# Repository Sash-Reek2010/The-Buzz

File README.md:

# The Buzz

A PCB which buzzes! You can change the tone and frequency using the potentiometers and make cool buzz combinations! It features the LM556 timer as the main IC here! The buzzers used here are passive piezo buzzers.

## Schematic
The schematic is made in KiCAD!

## PCB
The PCB is also made in KiCAD!

## PCB View & Render

## Try it out!

[KiCanvas Link](https://kicanvas.org/?repo=https%3A%2F%2Fgithub.com%2FSash-Reek2010%2FThe-Buzz%2Ftree%2Fmain%2FSource)

## BOM

| Name | Quantity |
|------|----------|
| Passive Piezo Buzzer | 10 |
| 10uF Capacitor | 2 |
| 10nF Capacitor | 2 |
| 100nF Capacitor | 1 |
| 100uF Capacitor | 1 |
| LM556 IC | 1 |
| USB A Connector | 1 |
| 10k Resistor | 2 |
| 10k Potentiometer | 2 |
| CD4017 IC | 1 |

## Thanks for Reading. - Sashreek!

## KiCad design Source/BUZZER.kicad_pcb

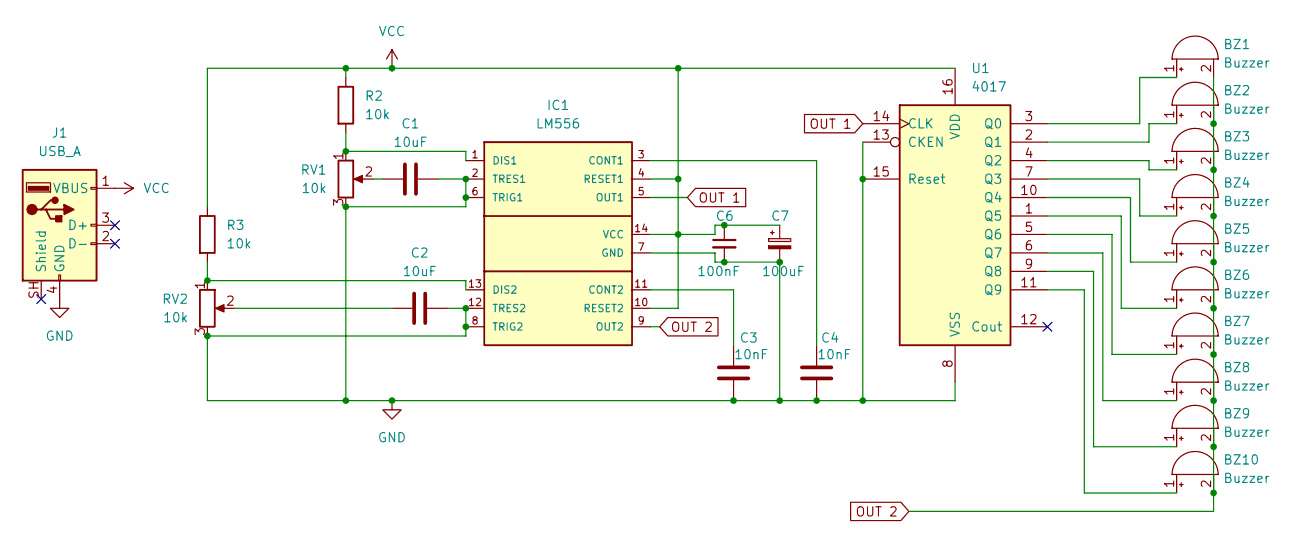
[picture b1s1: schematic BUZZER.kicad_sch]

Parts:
BZ1, BZ2, BZ3, BZ4, BZ5, BZ6, BZ7, BZ8, BZ9, BZ10: Buzzer; Buzzer_12x9.5RM7.6
C1, C2: 10uF; C_Disc_D8.0mm_W5.0mm_P5.00mm
C3, C4: 10nF; C_Disc_D8.0mm_W5.0mm_P5.00mm
C6: 100nF; C_Disc_D8.0mm_W5.0mm_P5.00mm
C7: 100uF; C_Radial_D5.0mm_H11.0mm_P2.00mm
IC1: LM556; DIL14; MPN NE556
J1: USB_A; USB_A_Molex_67643_Horizontal
R2, R3: 10k; R_Axial_DIN0204_L3.6mm_D1.6mm_P7.62mm_Horizontal
RV1, RV2: 10k; Potentiometer_Bourns_3386P_Vertical
U1: 4017; DIP-16_W7.62mm

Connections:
GND: C1.2, C2.1, C3.2, C4.2, C6.2, C7.2, IC1.2 (TRES1), IC1.6 (TRIG1), IC1.7 (GND), IC1.8 (TRIG2), IC1.12 (TRES2), J1.4 (GND), RV1.3, RV2.3, U1.8 (VSS), U1.13 (CKEN), U1.15 (Reset)
unnamed: BZ1.1 (+), U1.3 (Q0)
unnamed: BZ2.1 (+), U1.2 (Q1)
unnamed: BZ3.1 (+), U1.4 (Q2)
unnamed: BZ4.1 (+), U1.7 (Q3)
unnamed: BZ5.1 (+), U1.10 (Q4)
unnamed: BZ6.1 (+), U1.1 (Q5)
unnamed: BZ7.1 (+), U1.5 (Q6)
unnamed: BZ8.1 (+), U1.6 (Q7)
unnamed: BZ9.1 (+), U1.9 (Q8)
unnamed: BZ10.1 (+), U1.11 (Q9)
unnamed: C1.1, RV1.2
unnamed: C2.2, RV2.2
unnamed: C4.1, IC1.3 (CONT1)
unnamed: C3.1, IC1.11 (CONT2)
unnamed: IC1.1 (DIS1), R2.2, RV1.1
unnamed: IC1.13 (DIS2), R3.2, RV2.1
OUT 1: IC1.5 (OUT1), U1.14 (CLK)
OUT 2: BZ1.2 (-), BZ2.2 (-), BZ3.2 (-), BZ4.2 (-), BZ5.2 (-), BZ6.2 (-), BZ7.2 (-), BZ8.2 (-), BZ9.2 (-), BZ10.2 (-), IC1.9 (OUT2)
VCC: C6.1, C7.1, IC1.4 (RESET1), IC1.10 (RESET2), IC1.14 (VCC), J1.1 (VBUS), R2.1, R3.1, U1.16 (VDD)

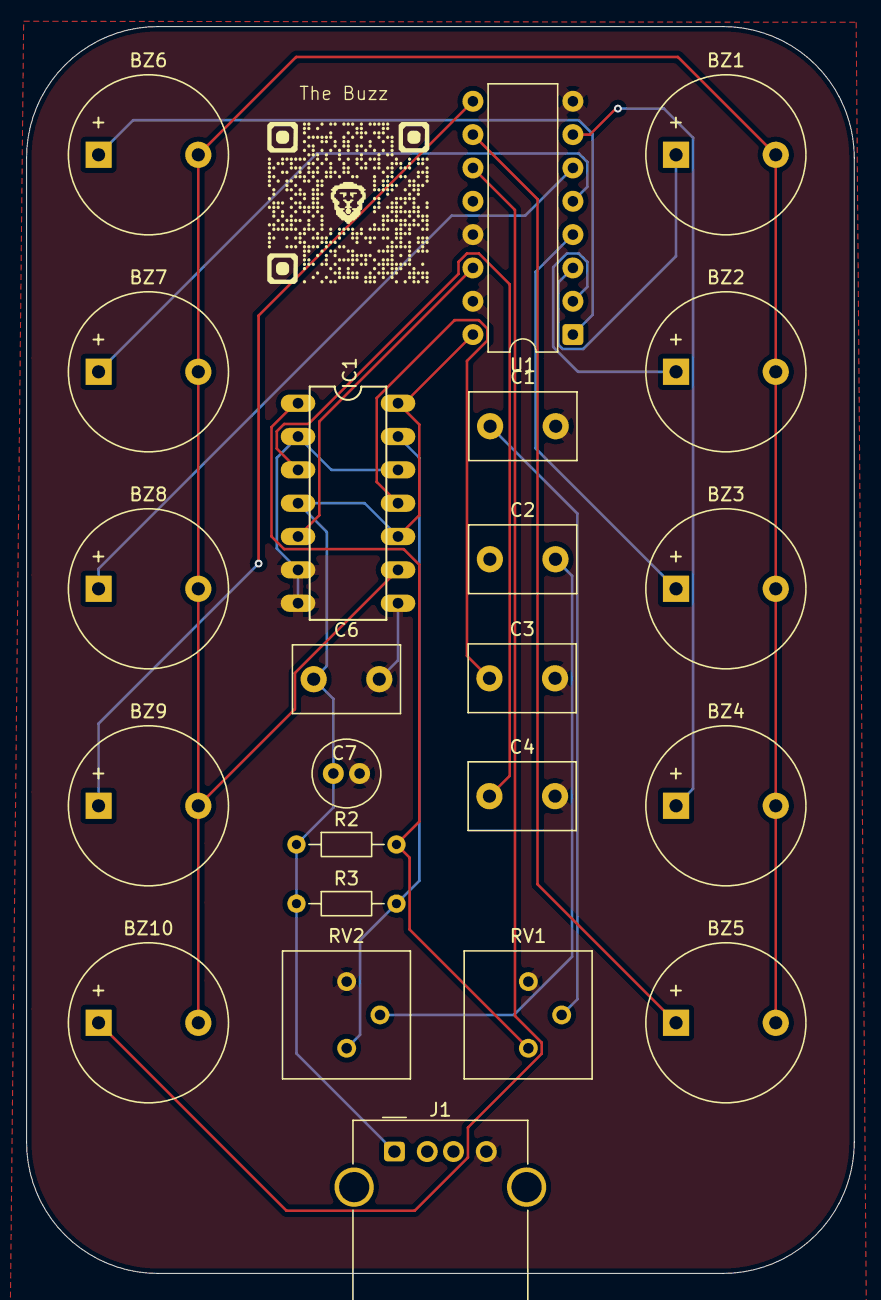
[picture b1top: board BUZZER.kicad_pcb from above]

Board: 2 copper layers, 63.1 x 95.0 mm, 24 parts (0 on the bottom side), 20 nets.

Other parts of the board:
.: LOGO

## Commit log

2026-05-25 Add Files
2026-05-27 Add Poster
2026-05-28 Add File
